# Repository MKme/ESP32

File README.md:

<p align="center">

<br>
🐦 <a href="https://twitter.com/mkmeorg">Twitter</a>
| 📺 <a href="https://www.youtube.com/mkmeorg">YouTube</a>
| 🌍 <a href="http://www.mkme.org">mkme.org</a><br>
Support this project and become a patron on <a href="http://mkme.org/patreon">Eric's Patreon</a>.<br>
Website, Forum and store are at http://mkme.org <br>
Chat with Me: <a href="https://discord.gg/j9S4Fgv">Discord</a></b>
</p>

Eric's ESP32 stuff for the various ESP32 boards and programming files in my collection.  Since the ESP32 is supported by MicroPython 
I will try to incorporate it in to more projects and videos as best I can.  

Buy an ESP32 Cam board here: https://amzn.to/2MMk2QP

Buy the ESP32 Lite Board here: https://amzn.to/2YDs3tN

Buy the OLED version here: https://amzn.to/36DUf4b

# Wemos ESP32 Lite Board

Buy the ESP 32 Lite on Amazon here: https://amzn.to/3coe2be

## Install Micropython

1.  Got to micropythong.org
2.  Download ESP32 Firmware for board
3.  Open Thonny and pick ESP32 on USB and flash firmware .bin
4.  Thonny Repl should be working  

## Wemos 32 Lite Reference Info Links

4MB Flash

Lithium battery interface, 500mA Max charging current

Default firmware: Lastest MicroPython firmware

Max serial baud rate: 256000bps

-  GPIO 22 has built in LED 

- No power LED so no wasted consumption

- https://diyprojects.io/wemos-lolin32-lite-compact-revision-lolin32-4-90/

- https://randomnerdtutorials.com/getting-started-micropython-esp32-esp8266/#:~:text=The%20code%20for%20blinking%20an%20LED%20on%20a,without%20the%20need%20to%20compile%20or%20upload%20code.

-  https://randomnerdtutorials.com/getting-started-micropython-esp32-esp8266/#:~:text=The%20code%20for%20blinking%20an%20LED%20on%20a,without%20the%20need%20to%20compile%20or%20upload%20code.

-  Not lite but same programming https://www.youtube.com/watch?v=BzAo48cFhS8&ab_channel=

# ESP 32 Cam Board

- See ResQ repo for updated ESP32 camera code but copied here for quick use

- Interesting Google Cam use https://www.youtube.com/watch?v=Upcr_rXnMQY&ab_channel=anyboards

- BME 280 I2C with ESP cam:  https://3iinc.xyz/blog/how-to-use-i2c-sensor-bme280-with-esp32cam/  

## FTDI Connections for programming: 
<br>

##  Arduino Settings for programming:

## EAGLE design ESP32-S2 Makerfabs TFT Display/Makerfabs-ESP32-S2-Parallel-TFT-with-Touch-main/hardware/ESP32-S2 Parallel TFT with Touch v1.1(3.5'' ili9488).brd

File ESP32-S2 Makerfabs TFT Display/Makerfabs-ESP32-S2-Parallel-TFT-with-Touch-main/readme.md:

# Makerfabs ESP32-S2 Parallel TFT with Touch

```c++
/*
Version:		V1.0
Author:			Vincent
Create Date:	2021/11/22
Note:
	
*/
```

[toc]

# Makerfabs

[Makerfabs home page](https://www.makerfabs.com/)

[Makerfabs Wiki](https://makerfabs.com/wiki/index.php?title=Main_Page)

# Makerfabs ESP32-S2 Parallel TFT with Touch
## Intruduce

Product Link ：[esp32-s2-parallel-tft-with-touch-3-5-ili9488](https://www.makerfabs.com/esp32-s2-parallel-tft-with-touch-3-5-ili9488.html) 

Wiki Link : [ESP32-S2 Parallel TFT with Touch(3.5'')](https://www.makerfabs.com/wiki/index.php?title=ESP32-S2_Parallel_TFT_with_Touch(3.5%27%27)) 

The 3.5" 320x480 TFT LCD driver is ILI9488, it uses 16bits parallel line for communication with ESP32-S2, the main clock could be up to 20MHz, make the display smooth enough for videos; You can freely use some of Mabee pins(A I2c and a IOs) with the breakout connectors, to connect the ESP32-S2 display with sensors/ actuators, suitable for IoT applications.

## Feature

- Integrated ESP32-S2 with 2.4G WiFi
- Wi-Fi Protocols: 802.11b/g/n(802.11n up to 150Mbps),A-MPDU and A-MSDU aggregation and 0.4us guard interval support
- Wi-Fi Frequency range: 2.402GHz - 2.483Ghz
- Arduino Compatible: You can play it with Arduino IDE
- LCD 3.5 inch Amorphous-TFT-LCD (Thin Film Transistor Liquid Crystal Display) for mobile-phone or handy electrical equipment
- LCD Driver: ILI9488(16bits parallel line)
- LCD Resolution: 320*480
- FT6236 Series ICs are single-chip capacitive touch panel controller IC with a built-in 16 bit enhanced Micro-controller unit (MCU)
- NS2009: A 4-wire resistive touch screen control circuit with I2C interface, which contains A 12-bit resolution A/D converter
- Power supply: 5V, Type-C USB
- Micro SD card slot on the board
- Dual USB Type-C: one for native USB and one for USB-to-UART
- Two Mabee interfaces
- Board size: 66mm * 85mm

# Code Explain

## Complier Option

- Install board : ESP32 .
- Install library : LovyanGFX library. 
- Edit the code based on the touch screen. If you use resistive screen, choice NS2009_TOUCH. If you use capacitive screen, choice FT6236_TOUCH. 
- Use type-c use cable connect USB-TTL to PC.
- Upload codes, select "ESP32-S2 DEV Module" and "UART0"

## Firmware

### SD16_3.5

Factory firmware. First run the boot self-test to check the hardware. Press down the middle of the touch screen as prompted to display a LOGO picture on the SD card. Finally, print the touch coordinates in the serial port.

## Example

### Simple Test

Three frame rate tests and SD card read and write tests.

- FillScreen

- Graph

- Touch

- PWM_backlight

Use pwm control screen back light.

### Display Demo

The display of 5 display effects is modified from Lovyan's example. There are also two homemade demonstration videos: ultrasonic ranging and line charts.

### Wifi Img

Receive TXT and BMP files over WIFI and display them on the screen.

Added a WiFi bulletin board app. You can upload and browse files in the SD card through the web page. And the latest uploaded BMP or TXT display on the 3.5-inch screen.

- Library Install：[esp32-micro-sdcard](https://github.com/nhatuan84/esp32-micro-sdcard) and [esp32-webserver](https://github.com/nhatuan84/esp32-webserver)
- Upload .\example\wifi_img_16\wifi_img_16.ino
- Insert the SD card and power on.
- Enter the IP address on the screen in your browser.

- Select TXT or BMP to be uploaded. BMP must be 480 x 320 pixels, 24 bits.

- Upload.
- Wait seconds, the content is displayed on the screen.

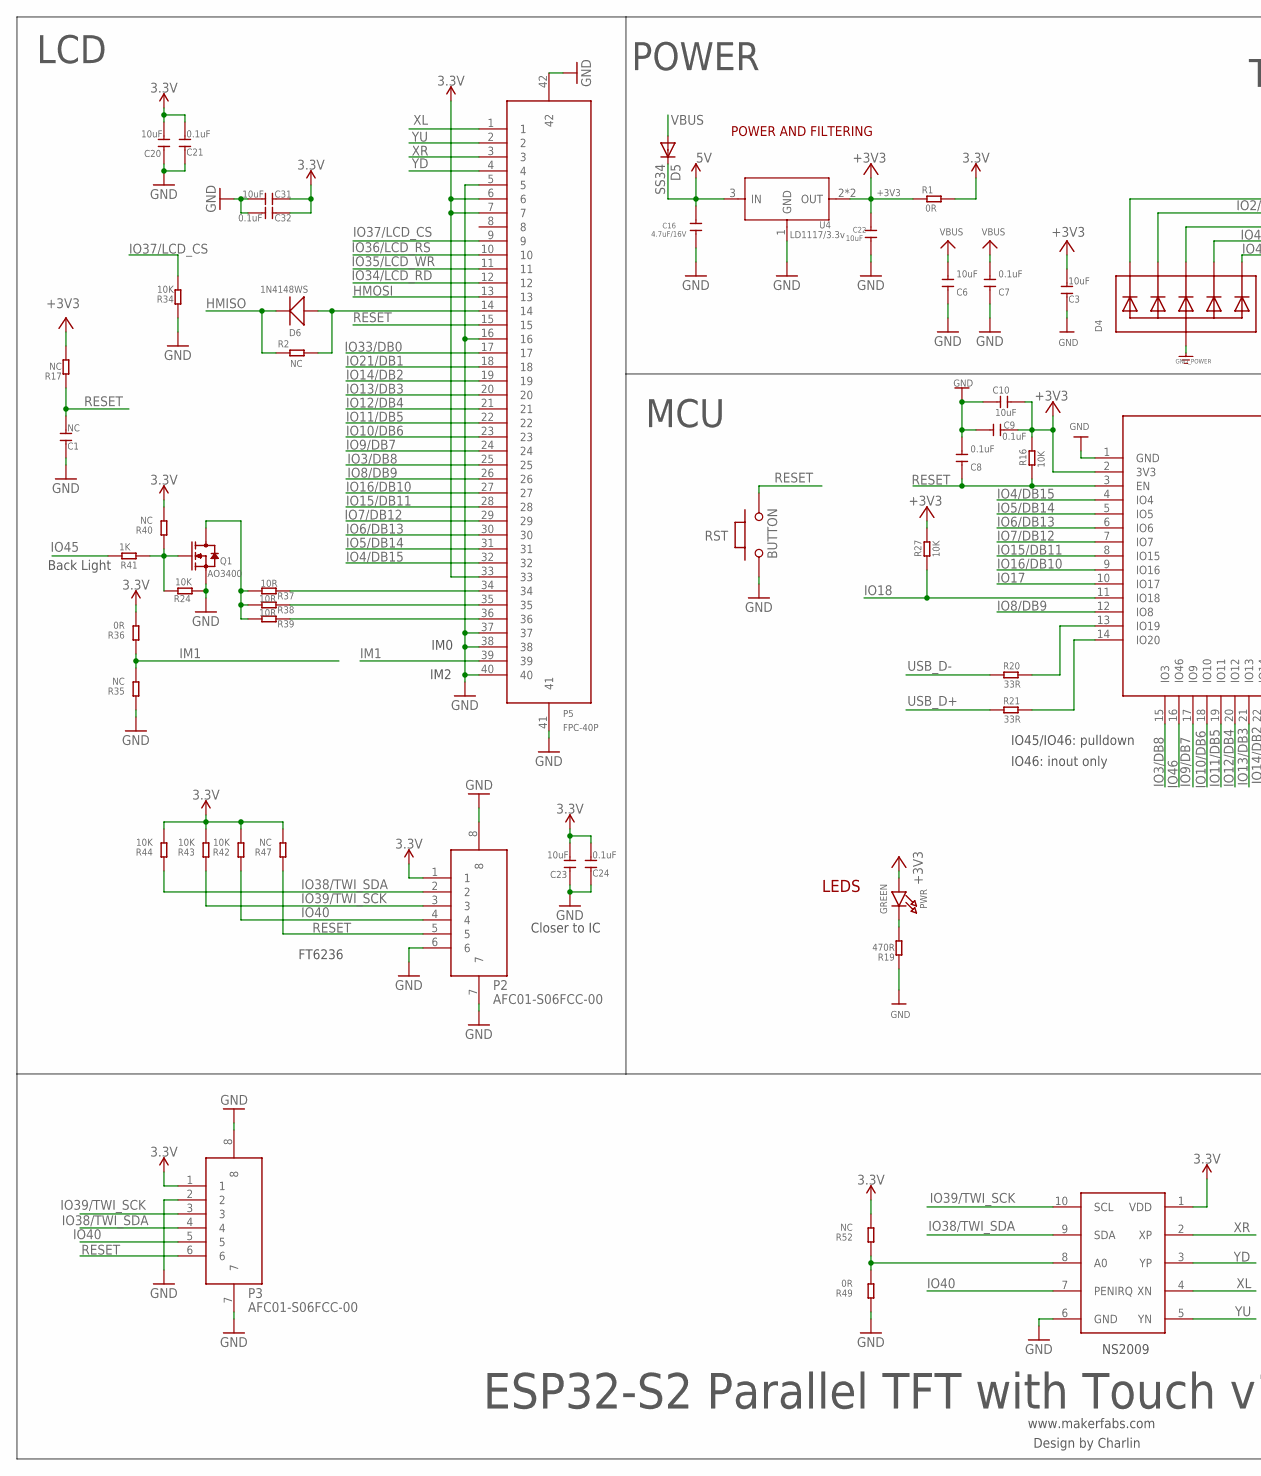
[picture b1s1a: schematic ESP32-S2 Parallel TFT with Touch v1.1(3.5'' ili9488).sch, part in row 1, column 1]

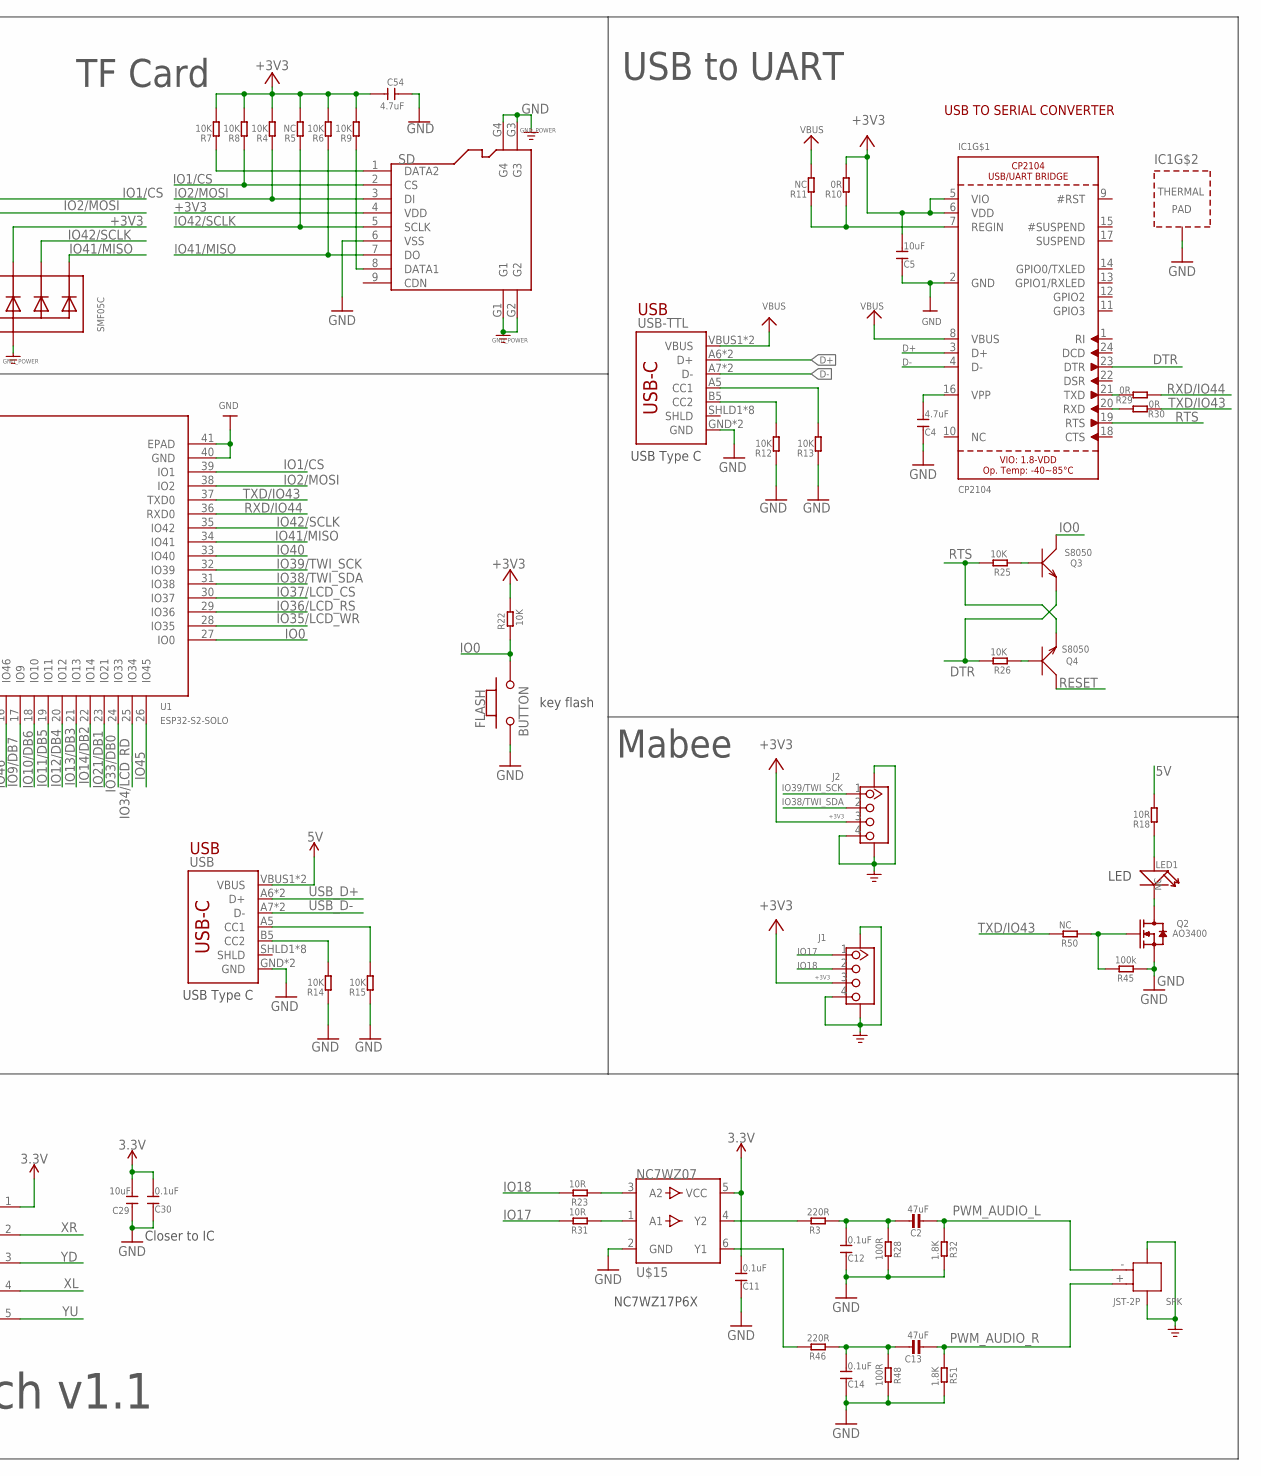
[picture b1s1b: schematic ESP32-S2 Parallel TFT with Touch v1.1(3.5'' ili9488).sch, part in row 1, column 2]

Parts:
C1: NC; DISCRETE_C0603
C2, C13: 47uF; MICROBUILDER_0805
C3, C5, C6, C10, C20, C23, C29, C31: 10uF; DISCRETE_C0603
C4, C54: 4.7uF; DISCRETE_C0603
C7, C8, C9, C11, C12, C14, C21, C24, C30, C32: 0.1uF; DISCRETE_C0603
C16: 4.7uF/16V; 0603
C22: 10uF; 0603
D4: SMF05C; SOT363
D5: SS34; DO-214AC
D6: 1N4148WS; SOD323
FLASH: BUTTON; 157SW
IC1: CP2104; QFN24_4MM_SMSC
J1, J2: GROVE-CONNECTOR-SMD'90D'; HW4-SMD-2.0-90D
LED1: NC; DISCRETE_LED-3528
P2, P3: AFC01-S06FCC-00; SMD8-50P-740L535W
P5: FPC-40P; SMD42-50P-2560L490W
PWR: GREEN; CHIPLED_0805_NOOUTLINE
Q1, Q2: AO3400; SOT23@1
Q3, Q4: S8050; SOT23
R1, R29, R30: 0R; R0603
R2, R50: NC; R0603
R3, R46: 220R; R0603
R4, R6, R7, R8, R9, R12, R13, R14, R15, R24, R34, R42, R43, R44: 10K; DISCRETE_R0603
R5, R11, R17, R35, R40, R47, R52: NC; DISCRETE_R0603
R10, R36, R49: 0R; DISCRETE_R0603
R16, R22, R25, R26, R27: 10K; R0603
R18, R37, R38, R39: 10R; DISCRETE_R0603
R19: 470R; DISCRETE_R0603
R20, R21: 33R; R0603
R23, R31: 10R; R0603
R28, R48: 100R; R0603
R32, R51: 1.8K; R0603
R41: 1K; DISCRETE_R0603
R45: 100k; R0603
RST: BUTTON; 157SW
SD: HOLDER-MICROSD-9P; 9P-SMD-W/-RING
SPK: JST-2P; HW2-SMD-2.0-90D
U1: ESP32­S2­SOLO; ESP32-­S2-­SOLO
U4: LD1117/3.3v; SOT89
U8: NS2009; MSOP10
U$15: NC7WZ07; SC70-6
USB: USB_C5; USB-C-16P-5
USB-TTL: USB_C5; USB-C-16P-5

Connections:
3.3V: C11.2, C20.2, C21.2, C23.2, C24.2, C29.2, C30.2, C31.1, C32.1, P2.1, P3.1, P5.6, P5.7, P5.33, R1.2, R36.2, R40.2, R42.2, R43.2, R44.2, R47.2, R52.2, U8.1 (VDD), U$15.5 (VCC)
5V: C16.1, D5.C, R18.2, U4.3 (IN), USB.VBUS1 (VBUS), USB.VBUS2 (VBUS)
+3V3: C3.2, C5.2, C9.1, C10.1, C22.1, C54.2, D4.4 (C3), IC1.5 (VIO), IC1.6 (VDD), J1.3, J2.3, PWR.A, R1.1, R4.2, R5.2, R6.2, R7.2, R8.2, R9.2, R10.2, R16.2, R17.2, R22.2, R27.2, SD.4 (VDD), U1.2 (3V3), U4.2 (OUT), U4.4 (OUT)
D+: IC1.3 (D+), USB-TTL.A6 (D+), USB-TTL.B6 (D+)
D-: IC1.4 (D-), USB-TTL.A7 (D-), USB-TTL.B7 (D-)
DTR: IC1.23 (DTR), Q3.2 (E), R26.2
GND: C1.1, C3.1, C4.1, C5.1, C6.1, C7.1, C8.2, C9.2, C10.2, C11.1, C12.1, C14.1, C16.2, C20.1, C21.1, C22.2, C23.1, C24.1, C29.1, C30.1, C31.2, C32.2, C54.1, D4.2 (A), FLASH.1, IC1.2 (GND), IC1.THERM (TP), J1.4, J1.SS1, J1.SS2, J2.4, J2.SS1, J2.SS2, P2.6, P2.7, P2.8, P3.2, P3.7, P3.8, P5.5, P5.16, P5.37, P5.38, P5.40, P5.41, P5.42, Q1.2 (S), Q2.2 (S), R12.1, R13.1, R14.1, R15.1, R19.1, R24.1, R28.2, R32.2, R34.1, R35.1, R45.1, R48.2, R49.1, R51.2, RST.1, SD.6 (VSS), SD.G1, SD.G2, SD.G3, SD.G4, SPK.3, SPK.4, U1.1 (GND), U1.40 (GND), U1.41 (EPAD), U4.1 (GND), U8.6 (GND), U$15.2 (GND), USB.GND, USB.GND2 (GND), USB-TTL.GND, USB-TTL.GND2 (GND)
HMISO: D6.-, R2.1
HMOSI: P5.13
IM1: P5.39, R35.2, R36.1
IO0: FLASH.2, Q3.3 (C), R22.1, U1.27 (IO0)
IO1/CS: D4.1 (C1), R8.1, SD.2 (CS), U1.39 (IO1)
IO2/MOSI: D4.3 (C2), R4.1, SD.3 (DI), U1.38 (IO2)
IO3/DB8: P5.25, U1.15 (IO3)
IO4/DB15: P5.32, U1.4 (IO4)
IO5/DB14: P5.31, U1.5 (IO5)
IO6/DB13: P5.30, U1.6 (IO6)
IO7/DB12: P5.29, U1.7 (IO7)
IO8/DB9: P5.26, U1.12 (IO8)
IO9/DB7: P5.24, U1.17 (IO9)
IO10/DB6: P5.23, U1.18 (IO10)
IO11/DB5: P5.22, U1.19 (IO11)
IO12/DB4: P5.21, U1.20 (IO12)
IO13/DB3: P5.20, U1.21 (IO13)
IO14/DB2: P5.19, U1.22 (IO14)
IO15/DB11: P5.28, U1.8 (IO15)
IO16/DB10: P5.27, U1.9 (IO16)
IO17: J1.1, R31.2, U1.10 (IO17)
IO18: J1.2, R23.2, R27.1, U1.11 (IO18)
IO21/DB1: P5.18, U1.23 (IO21)
IO33/DB0: P5.17, U1.24 (IO33)
IO34/LCD_RD: P5.12, U1.25 (IO34)
IO35/LCD_WR: P5.11, U1.28 (IO35)
IO36/LCD_RS: P5.10, U1.29 (IO36)
IO37/LCD_CS: P5.9, R34.2, U1.30 (IO37)
IO38/TWI_SDA: J2.2, P2.2, P3.4, R44.1, U1.31 (IO38), U8.9 (SDA)
IO39/TWI_SCK: J2.1, P2.3, P3.3, R43.1, U1.32 (IO39), U8.10 (SCL)
IO40: P2.4, P3.5, R42.1, U1.33 (IO40), U8.7 (PENIRQ)
IO41/MISO: D4.6 (C5), R6.1, SD.7 (DO), U1.34 (IO41)
IO42/SCLK: D4.5 (C4), R5.1, SD.5 (SCLK), U1.35 (IO42)
IO45: R41.2, U1.26 (IO45)
IO46: U1.16 (IO46)
unnamed: C4.2, IC1.16 (VPP)
unnamed: Q4.1 (B), R26.1
unnamed: Q3.1 (B), R25.1
unnamed: D6.+, P5.14, R2.2
unnamed: Q2.1 (G), R45.2, R50.1
unnamed: R15.2, USB.A5 (CC1)
unnamed: PWR.C, R19.2
unnamed: LED1.1 (+), R18.1
unnamed: LED1.2 (-), Q2.3 (D)
unnamed: R13.2, USB-TTL.A5 (CC1)
unnamed: R12.2, USB-TTL.B5 (CC2)
unnamed: IC1.7 (REGIN), R10.1, R11.1
unnamed: R3.2, U$15.4 (Y2)
unnamed: R14.2, USB.B5 (CC2)
unnamed: R20.2, U1.13 (IO19)
unnamed: R21.2, U1.14 (IO20)
unnamed: C2.1, C12.2, R3.1, R28.1
unnamed: IC1.21 (TXD), R29.2
unnamed: IC1.20 (RXD), R30.2
unnamed: P5.34, R37.1
unnamed: P5.35, R38.1
unnamed: P5.36, R39.1
unnamed: Q1.1 (G), R24.2, R40.1, R41.1
unnamed: Q1.3 (D), R37.2, R38.2, R39.2
unnamed: R49.2, R52.1, U8.8 (A0)
unnamed: R46.2, U$15.6 (Y1)
unnamed: R23.1, U$15.3 (A2)
unnamed: R31.1, U$15.1 (A1)
unnamed: C13.1, C14.2, R46.1, R48.1
unnamed: R7.1, SD.1 (DATA2)
unnamed: R9.1, SD.8 (DATA1)
PWM_AUDIO_L: C2.2, R32.1, SPK.- (2)
PWM_AUDIO_R: C13.2, R51.1, SPK.+ (1)
RESET: C1.2, C8.1, P2.5, P3.6, P5.15, Q4.3 (C), R16.1, R17.1, R47.1, RST.2, U1.3 (EN)
RTS: IC1.19 (RTS), Q4.2 (E), R25.2
RXD/IO44: R29.1, U1.36 (RXD0)
TXD/IO43: R30.1, R50.2, U1.37 (TXD0)
USB_D+: R21.1, USB.A6 (D+), USB.B6 (D+)
USB_D-: R20.1, USB.A7 (D-), USB.B7 (D-)
VBUS: C6.2, C7.2, D5.A, IC1.8 (VBUS), R11.2, USB-TTL.VBUS1 (VBUS), USB-TTL.VBUS2 (VBUS)
XL: P5.1, U8.4 (XN)
XR: P5.3, U8.2 (XP)
YD: P5.4, U8.3 (YP)
YU: P5.2, U8.5 (YN)

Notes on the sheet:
www.makerfabs.com
Design by Charlin
USB
LEDS
POWER AND FILTERING
USB TO SERIAL CONVERTER
key flash
ESP32-S2 Parallel TFT with Touch v1.1
POWER
USB to UART
USB Type C
TF Card
LED
NS2009
FT6236
Closer to IC
Back Light
IM0
IM2
IO45/IO46: pulldown
IO46: inout only
NC7WZ17P6X
Mabee
LCD
MCU

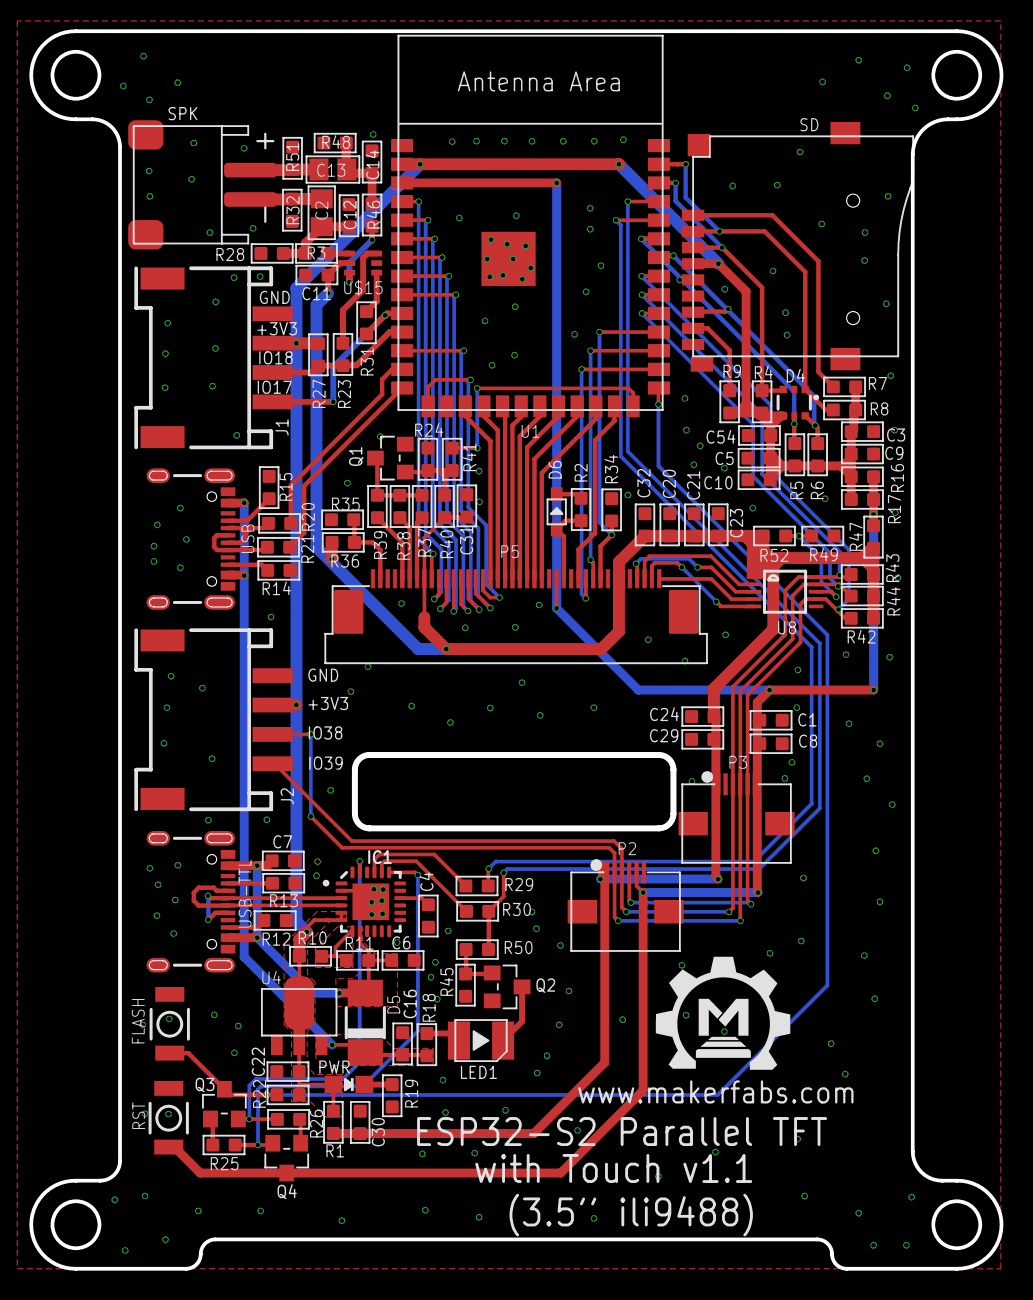
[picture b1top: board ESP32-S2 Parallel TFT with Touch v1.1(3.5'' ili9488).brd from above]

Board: 2 copper layers, 65.9 x 84.1 mm, 102 parts (0 on the bottom side), 84 nets.

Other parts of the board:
U$1: MAKERFABS_0.3

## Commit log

2021-02-03 ESP32 Handy dandy
2021-02-03 ESP32Cam
2021-02-06 Wemos 32 Lite Notes and info
2021-02-06 32 lite
2021-04-19 Arduino IDE updates
2021-04-23 Created KiCad Library files
    Bought from fiverr
2021-04-28 Cam stuff
2021-05-08 WROOM
2021-09-05 Breakout board Build
2021-10-10 Photos and kit updated
2021-10-16 Breakout board DONE
2021-11-25 Breakout added
2021-12-30 Final pics
2022-01-21 Added S2
2022-02-04 Fixes

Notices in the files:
parts and their libraries:
microbuilder: This work is placed in the public domain, and may be freely used for commercial and non-commercial work with the following conditions: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
SparkFun-Retired: Licensing: Creative Commons ShareAlike 4.0 International - https://creativecommons.org/licenses/by-sa/4.0
